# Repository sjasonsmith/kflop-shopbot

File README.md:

# kflop-shopbot
Custom KFLOP operations for a repowered ShopBot Buddy with speed controlled spindle.

**Caution: These scripts are not guaranteed to work on your machine.
Use at your own risk, and only with a full understanding of the functionality you are using.**

These scripts were developed for a ShopBot Buddy which has been repowered with a Dynomotion KFLOP Motion Controller. Refer to the following forum for a description of the conversion:

https://www.cnczone.com/forums/dynomotion-kflop-kanalog/310688-software.html

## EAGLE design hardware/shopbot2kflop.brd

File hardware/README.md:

# kflop-shopbot
EAGLE resources to create an interface board between the KMotion KFlop and the ShopBot Buddy.
This enables the conversion without modifying any existing electronics.

Board layout

Schematic

Additional Information:

https://www.cnczone.com/forums/dynomotion-kflop-kanalog/310688-software.html

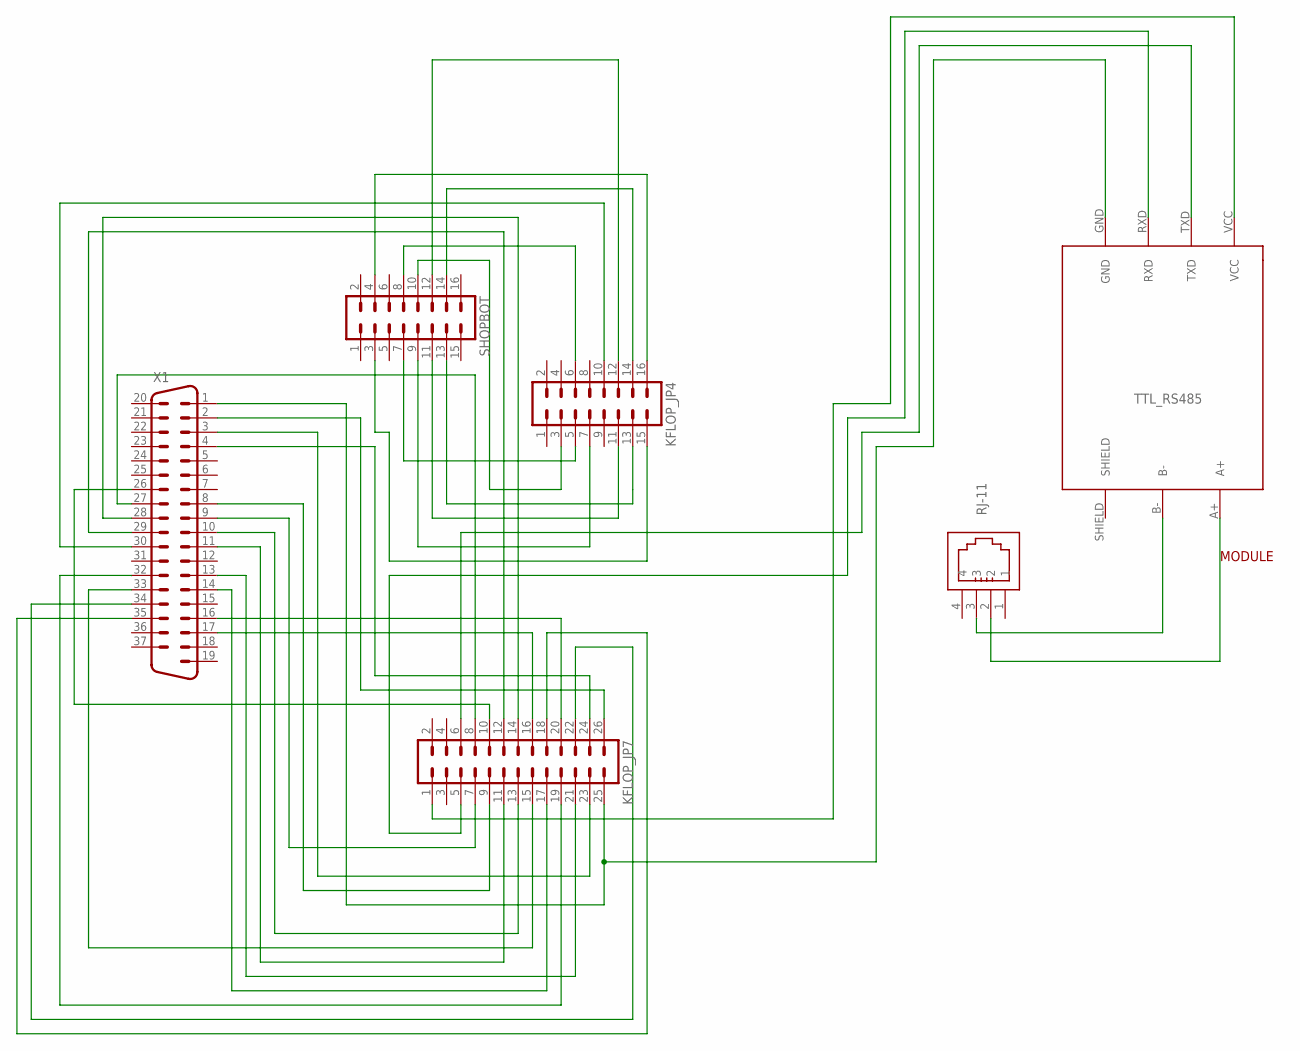
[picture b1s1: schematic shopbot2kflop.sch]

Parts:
KFLOP_JP4: MA08-2
KFLOP_JP7: MA13-2
MODULE: TTL_RS485
RJ-11: 615004144121
SHOPBOT: MA08-2
X1: M37HP

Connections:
unnamed: KFLOP_JP7.13, X1.10
unnamed: KFLOP_JP4.6, SHOPBOT.8
unnamed: KFLOP_JP7.18, X1.35
unnamed: KFLOP_JP7.5, MODULE.RXD
unnamed: KFLOP_JP7.26, X1.2
unnamed: KFLOP_JP7.6, MODULE.TXD
unnamed: KFLOP_JP4.5, SHOPBOT.7
unnamed: KFLOP_JP4.3, SHOPBOT.10
unnamed: KFLOP_JP4.15, SHOPBOT.3
unnamed: KFLOP_JP4.16, SHOPBOT.4
unnamed: KFLOP_JP4.7, SHOPBOT.9
unnamed: MODULE.B-, RJ-11.3
unnamed: KFLOP_JP7.23, X1.3
unnamed: KFLOP_JP7.24, X1.4
unnamed: KFLOP_JP7.9, X1.8
unnamed: KFLOP_JP7.7, X1.9
unnamed: KFLOP_JP7.1, MODULE.VCC
unnamed: KFLOP_JP7.11, X1.11
unnamed: KFLOP_JP7.21, X1.13
unnamed: KFLOP_JP7.17, X1.14
unnamed: KFLOP_JP7.20, X1.16
unnamed: KFLOP_JP7.16, X1.17
unnamed: KFLOP_JP7.10, X1.26
unnamed: KFLOP_JP7.8, X1.27
unnamed: KFLOP_JP7.14, X1.28
unnamed: KFLOP_JP7.12, X1.29
unnamed: KFLOP_JP4.10, X1.30
unnamed: KFLOP_JP7.19, X1.32
unnamed: KFLOP_JP7.15, X1.33
unnamed: KFLOP_JP7.22, X1.34
unnamed: KFLOP_JP4.11, SHOPBOT.11
unnamed: KFLOP_JP7.25, MODULE.GND, X1.1
unnamed: MODULE.A+, RJ-11.2
unnamed: KFLOP_JP4.12, SHOPBOT.12
unnamed: KFLOP_JP4.13, SHOPBOT.13
unnamed: KFLOP_JP4.14, SHOPBOT.14

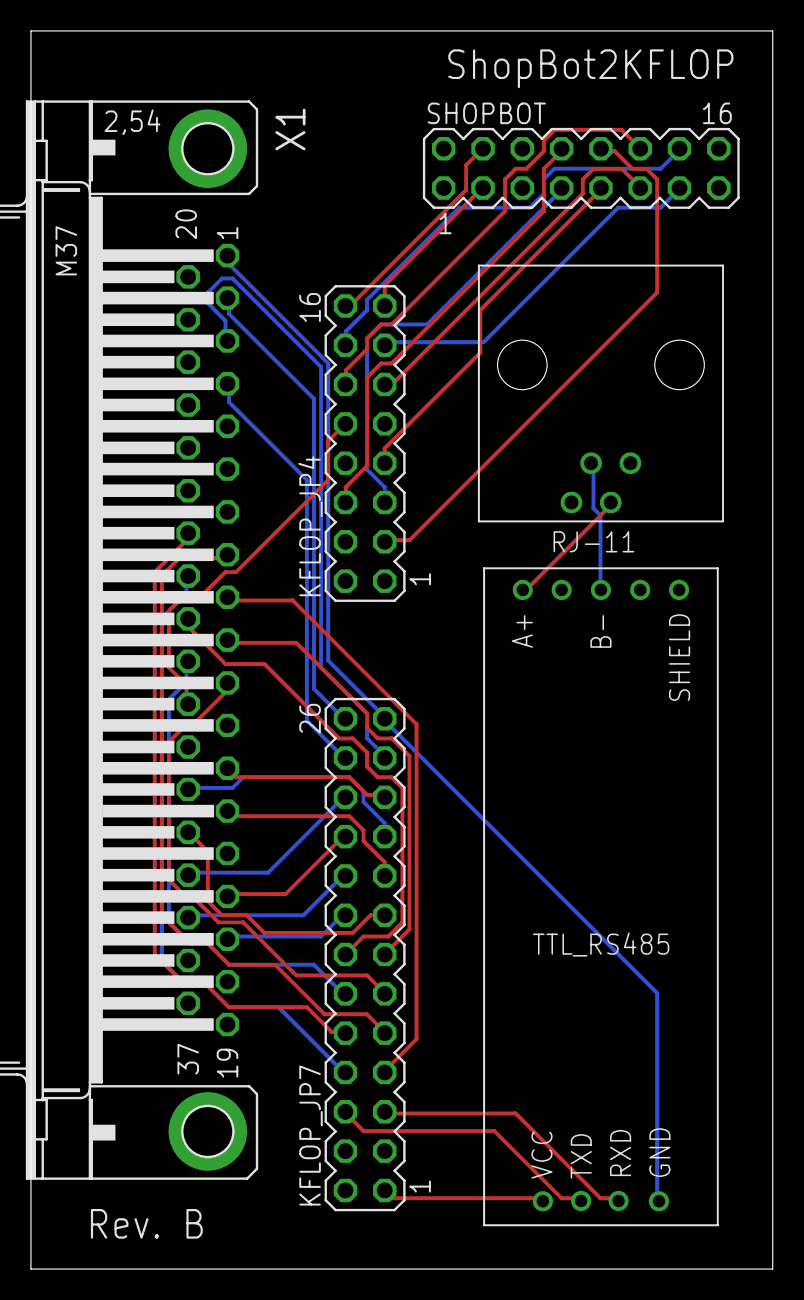
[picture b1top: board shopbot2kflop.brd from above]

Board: 2 copper layers, 47.9 x 80.0 mm, 6 parts (0 on the bottom side), 36 nets.

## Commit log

2016-05-18 Initial checkin of MosbusMaster
    This is intended for an I/O expander, we will need to modify it to talk to
    our spindle.
2016-05-18 Add header needed by original program
2016-05-19 Add .gitignore to ignore .out and temporary files
2016-05-19 Jason's hacky version which will turn on the spindle
2016-05-19 Remove non-buffered serial code
2016-05-19 Add init and homig scripts
2016-05-19 Add SafeZ program
2016-05-20 Add simple program to fake setting spindle speed
2016-05-20 Remove Modbusmaster folder
2016-05-24 Fix issue with retracting when pausing a job. Now goes to machine 0 when paused.
2016-05-27 Fix SafeZ_SpindleOff and add new ZHeight program.
2016-05-27 Add speed control support.
2016-05-27 Disable Modbus I/O and talk between threads
    SetSpindleSpeed will set a desired speed, and wait until the modbus master
    thread echoes the value back.
2016-05-27 Print status every 5 second
2016-05-27 Add loops for spindle on/off using virtual bits
2016-05-27 Use virtual bits to control spindle state. Does not yet control speed.
2016-05-27 Working ZHeight probe
2016-05-27 Launch modbus thread from Init thread.
2016-05-27 Home Z axis before X and Y.
2016-05-27 Add ToolCheck command
2016-05-27 Add commands that start spindle then wait 4 second.
2018-05-01 Modify soft limit for new bed height. Replaced MDF bed with aluminum and need more travel range.
2018-05-01 Add script which is deployed to KMotion. Not sure if it is being used.
2018-05-01 Move source files into subfolder
2018-05-01 Add screenshots of configuration in KMotionCNC
2018-06-15 Move ModbusMaster to thread 1
    This allows the thread to keep running when stop is pressed so that it can
    be used to stop the spindle.
2018-06-15 Add snapshot of data folder, which stores configuration
2018-06-15 Add a hack to stop the spindle when INIT is re-run
2019-01-20 Add Eagle resources for the interface board used This avoided modifications to the original ShopBot controller, by allowing direct connections to the KFlop.
2019-01-20 Add images to readme page in hardware folder
2019-01-20 Add pinout.

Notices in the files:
parts and their libraries:
Wurth_Elektronik_Electromechanic_Input-O: Copyright: Würth Elektronik
